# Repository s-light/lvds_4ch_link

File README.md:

<!--lint disable list-item-indent-->
<!--lint disable list-item-bullet-indent-->

# lvds_4ch_link
Simple LVDS 4ch Link over network-patch-cable

can be used for SPI, UART or simple GPIO

- Receiver: TI [SN65LVDT348](http://www.ti.com/product/SN65LVDT348)
- Driver: TI [SN65LVDS391](http://www.ti.com/product/SN65LVDS391)

---

# License
<!-- license info -->

<br />
<span xmlns:dct="http://purl.org/dc/terms/" property="dct:title">
    lvds_4ch_link
</span> by
<a xmlns:cc="http://creativecommons.org/ns#"
        href="https://github.com/s-light/lvds_4ch_link/"
        property="cc:attributionName"
        rel="cc:attributionURL">
    Stefan Krüger (s-light)
</a>
is licensed under a<br/>
<a rel="license" href="http://creativecommons.org/licenses/by/4.0/">
    Creative Commons Attribution 4.0 International License
</a>.
<!-- license info end -->

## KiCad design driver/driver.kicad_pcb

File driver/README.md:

# XXXXXXXXX Board-Name / Title XXXXXXXXX

some description..

---

<!-- license info -->

<br />
<span xmlns:dct="http://purl.org/dc/terms/" property="dct:title">
    XXXXXXXXX Board-Name / Title XXXXXXXXX
</span> by
<a xmlns:cc="http://creativecommons.org/ns#"
        href="https://github.com/s-light/"
        property="cc:attributionName"
        rel="cc:attributionURL">
    Stefan Krüger (s-light)
</a>
is licensed under a<br/>
<a rel="license" href="http://creativecommons.org/licenses/by/4.0/">
    Creative Commons Attribution 4.0 International License
</a>.
<!-- license info end -->

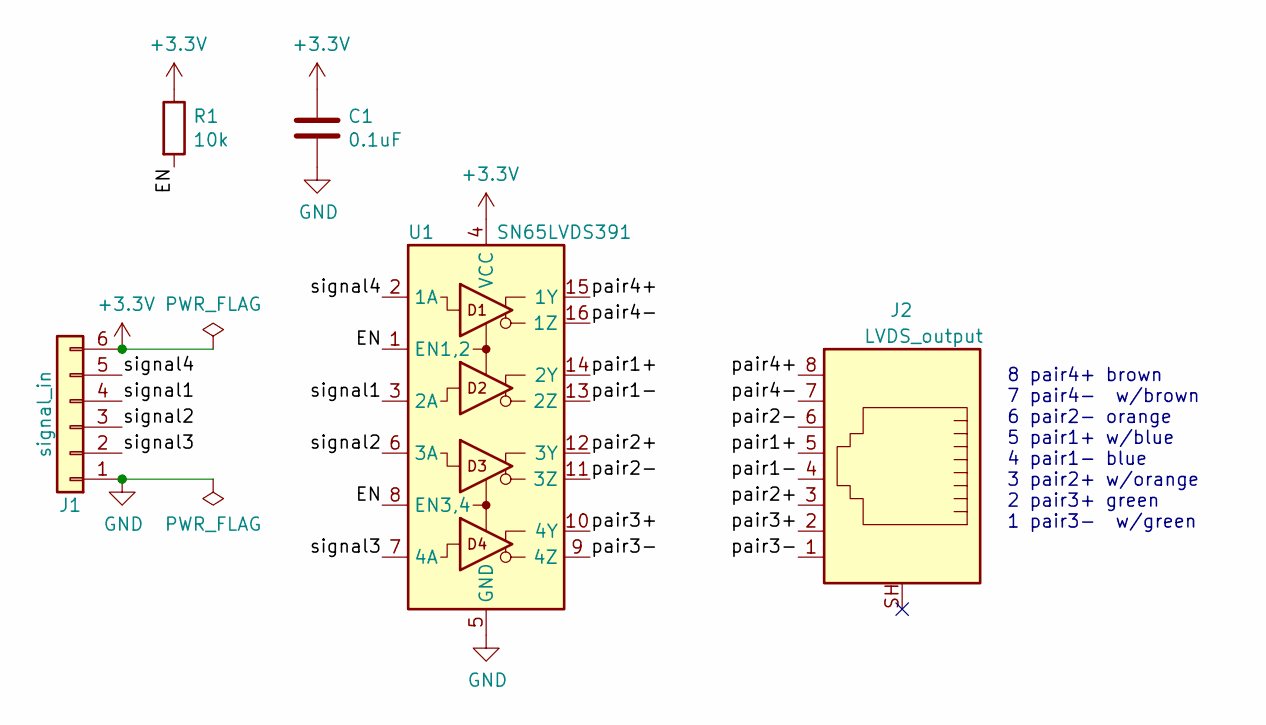
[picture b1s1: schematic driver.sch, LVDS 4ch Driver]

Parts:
C1: 0.1uF; C_0603_1608Metric_Pad1.05x0.95mm_HandSolder
J1: signal_in; PinHeader_1x06_P2.54mm_Horizontal
J2: LVDS_output; RJ45_Stewart_SS-6488S-A-NF
R1: 10k; R_1206_3216Metric_Pad1.42x1.75mm_HandSolder
U1: SN65LVDS391; SOIC-16_3.9x9.9mm_P1.27mm

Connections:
+3V3: C1.1, J1.6, R1.1, U1.4 (VCC)
/EN: R1.2, U1.1 (EN1,2), U1.8 (EN3,4)
/pair1+: J2.5, U1.14 (2Y)
/pair1-: J2.4, U1.13 (2Z)
/pair2+: J2.3, U1.12 (3Y)
/pair2-: J2.6, U1.11 (3Z)
/pair3+: J2.2, U1.10 (4Y)
/pair3-: J2.1, U1.9 (4Z)
/pair4+: J2.8, U1.15 (1Y)
/pair4-: J2.7, U1.16 (1Z)
/signal1: J1.4, U1.3 (2A)
/signal2: J1.3, U1.6 (3A)
/signal3: J1.2, U1.7 (4A)
/signal4: J1.5, U1.2 (1A)
GND: C1.2, J1.1, U1.5 (GND)

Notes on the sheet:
8 pair4+ brown 7 pair4- w/brown 6 pair2- orange 5 pair1+ w/blue 4 pair1- blue 3 pair2+ w/orange 2 pair3+ green 1 pair3- w/green

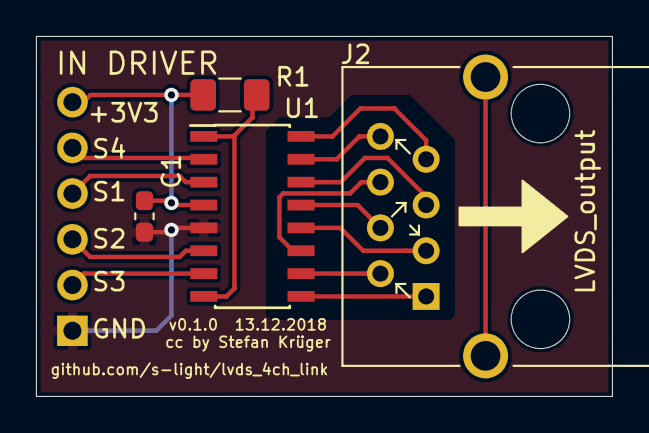
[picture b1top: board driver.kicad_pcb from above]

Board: 2 copper layers, 32.0 x 20.0 mm, 5 parts (1 on the bottom side), 15 nets.

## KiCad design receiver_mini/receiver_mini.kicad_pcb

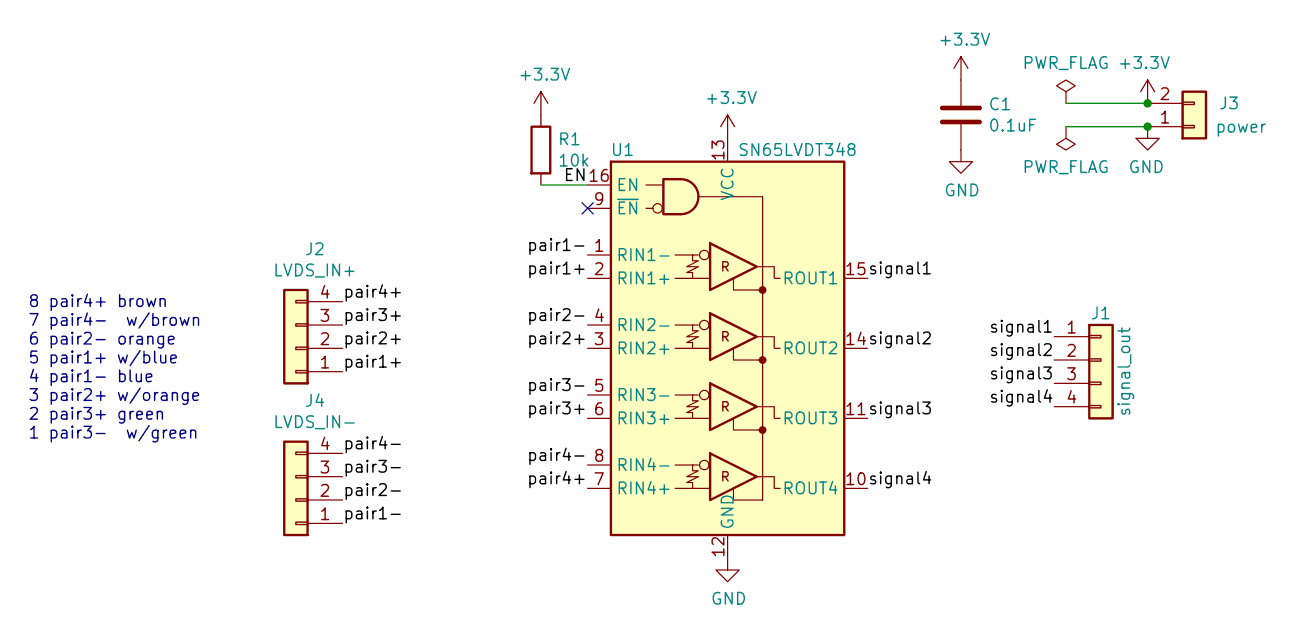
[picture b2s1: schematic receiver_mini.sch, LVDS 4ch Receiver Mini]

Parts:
C1: 0.1uF; C_0603_1608Metric_Pad1.05x0.95mm_HandSolder
J1: signal_out; PinHeader_1x04_P2.54mm_Vertical
J2: LVDS_IN+; PinHeader_1x04_P2.54mm_Vertical
J3: power; PinHeader_1x02_P2.54mm_Vertical
J4: LVDS_IN-; PinHeader_1x04_P2.54mm_Vertical
R1: 10k; R_0603_1608Metric_Pad1.05x0.95mm_HandSolder
U1: SN65LVDT348; SOIC-16_3.9x9.9mm_P1.27mm

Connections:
+3V3: C1.1, J3.2, R1.1, U1.13 (VCC)
/EN: R1.2, U1.16 (EN)
/pair1+: J2.1, U1.2 (RIN1+)
/pair1-: J4.1, U1.1 (RIN1-)
/pair2+: J2.2, U1.3 (RIN2+)
/pair2-: J4.2, U1.4 (RIN2-)
/pair3+: J2.3, U1.6 (RIN3+)
/pair3-: J4.3, U1.5 (RIN3-)
/pair4+: J2.4, U1.7 (RIN4+)
/pair4-: J4.4, U1.8 (RIN4-)
/signal1: J1.1, U1.15 (ROUT1)
/signal2: J1.2, U1.14 (ROUT2)
/signal3: J1.3, U1.11 (ROUT3)
/signal4: J1.4, U1.10 (ROUT4)
GND: C1.2, J3.1, U1.12 (GND)

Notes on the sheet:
8 pair4+ brown 7 pair4- w/brown 6 pair2- orange 5 pair1+ w/blue 4 pair1- blue 3 pair2+ w/orange 2 pair3+ green 1 pair3- w/green

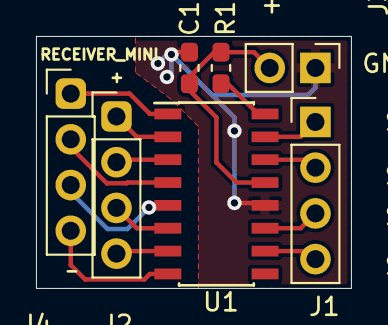
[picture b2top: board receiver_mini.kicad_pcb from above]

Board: 2 copper layers, 17.5 x 14.0 mm, 7 parts (0 on the bottom side), 15 nets.

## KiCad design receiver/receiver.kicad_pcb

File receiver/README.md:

# LVDS 4ch Link - Receiver

for now have a look at the main [readme](../README.md)

---

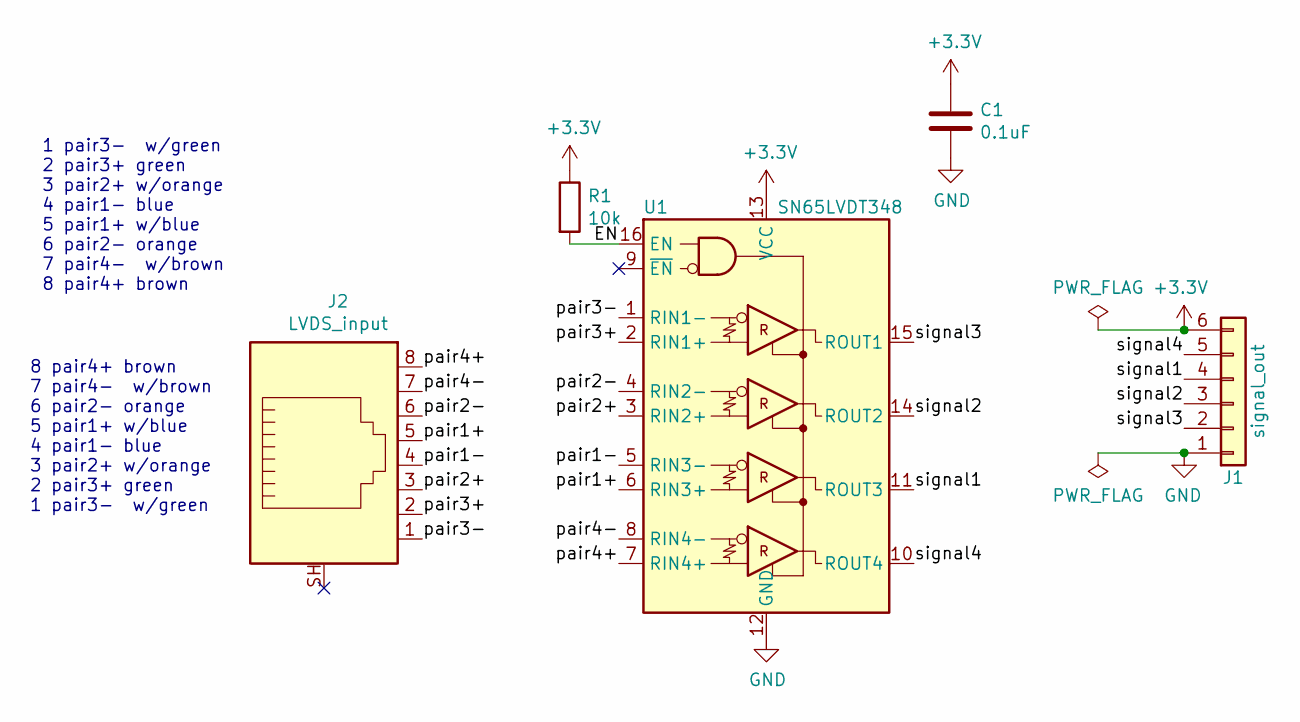
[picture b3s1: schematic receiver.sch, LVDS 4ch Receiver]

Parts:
C1: 0.1uF; C_0603_1608Metric_Pad1.05x0.95mm_HandSolder
J1: signal_out; PinHeader_1x06_P2.54mm_Horizontal
J2: LVDS_input; RJ45_Stewart_SS-6488S-A-NF
R1: 10k; R_1206_3216Metric_Pad1.42x1.75mm_HandSolder
U1: SN65LVDT348; SOIC-16_3.9x9.9mm_P1.27mm

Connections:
+3V3: C1.1, J1.6, R1.1, U1.13 (VCC)
/EN: R1.2, U1.16 (EN)
/pair1+: J2.5, U1.6 (RIN3+)
/pair1-: J2.4, U1.5 (RIN3-)
/pair2+: J2.3, U1.3 (RIN2+)
/pair2-: J2.6, U1.4 (RIN2-)
/pair3+: J2.2, U1.2 (RIN1+)
/pair3-: J2.1, U1.1 (RIN1-)
/pair4+: J2.8, U1.7 (RIN4+)
/pair4-: J2.7, U1.8 (RIN4-)
/signal1: J1.4, U1.11 (ROUT3)
/signal2: J1.3, U1.14 (ROUT2)
/signal3: J1.2, U1.15 (ROUT1)
/signal4: J1.5, U1.10 (ROUT4)
GND: C1.2, J1.1, U1.12 (GND)

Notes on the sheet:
1 pair3- w/green 2 pair3+ green 3 pair2+ w/orange 4 pair1- blue 5 pair1+ w/blue 6 pair2- orange 7 pair4- w/brown 8 pair4+ brown
8 pair4+ brown 7 pair4- w/brown 6 pair2- orange 5 pair1+ w/blue 4 pair1- blue 3 pair2+ w/orange 2 pair3+ green 1 pair3- w/green

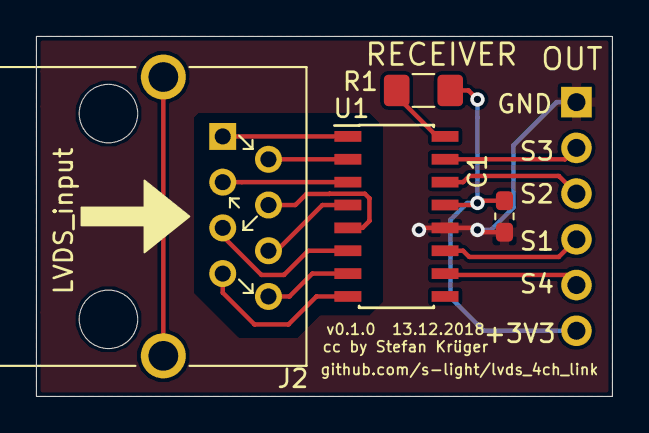
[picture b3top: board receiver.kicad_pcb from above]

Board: 2 copper layers, 32.0 x 20.0 mm, 5 parts (1 on the bottom side), 15 nets.

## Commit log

2018-12-13 prepared receiver
2018-12-13 prepaired link
2018-12-13 prepare driver
2018-12-13 basic placement + added pullup for EN
2018-12-13 changed to correct RJ45-Plug
2018-12-13 Driver finalized
2018-12-13 exported..
2018-12-13 added images in docu
2018-12-14 added receiver_mini
2018-12-14 added receiver_mini images to readme
2018-12-14 added 3d model simplified
2019-01-13 better readability in pcb
2019-01-13 better readabillity in pcb

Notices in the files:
driver/README.md:
<img alt="Creative Commons License" style="border-width:0"
src="https://i.creativecommons.org/l/by/4.0/88x31.png" />
driver/driver.kicad_pcb:
CC BY
cc by Stefan Krüger
